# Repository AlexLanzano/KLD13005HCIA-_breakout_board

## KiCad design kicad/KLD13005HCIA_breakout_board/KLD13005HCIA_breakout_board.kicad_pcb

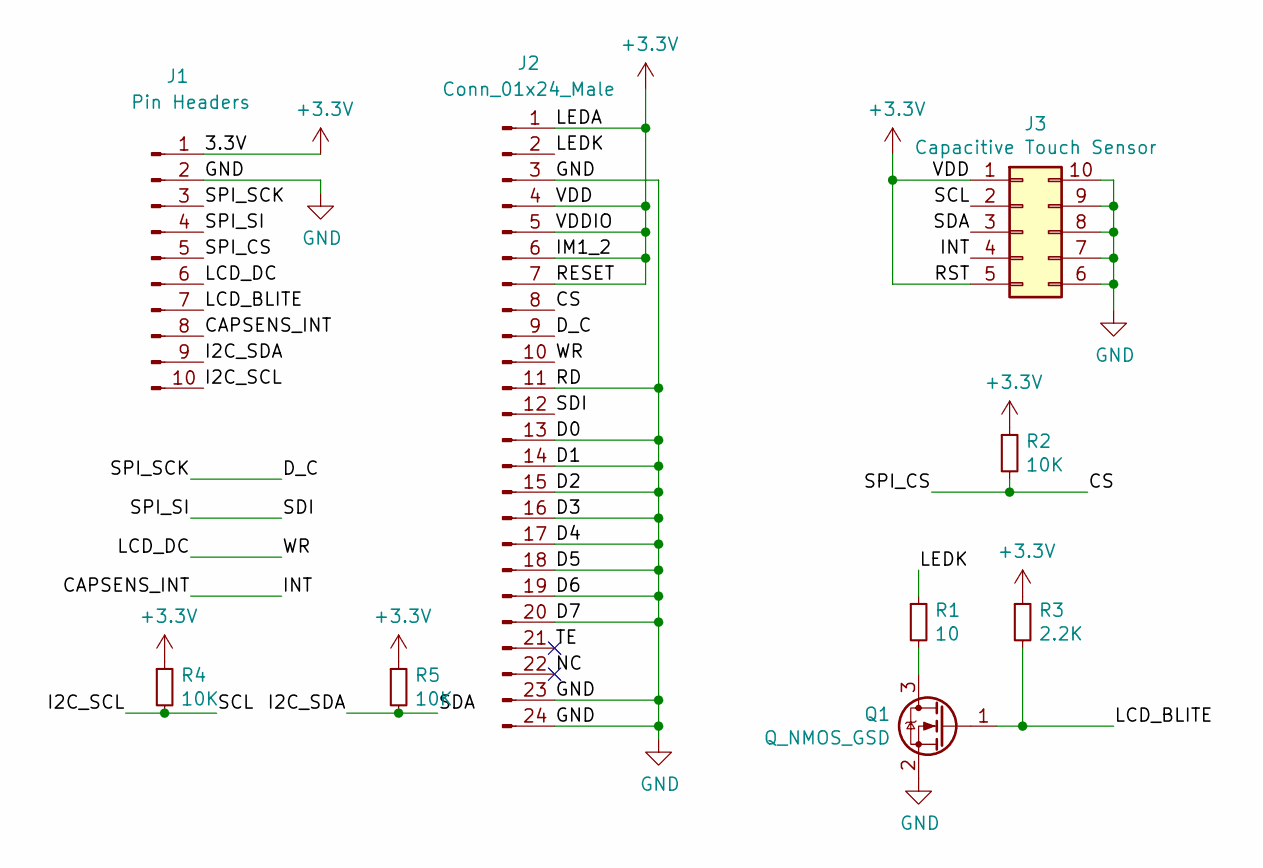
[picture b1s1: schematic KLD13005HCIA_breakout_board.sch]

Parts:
J1: Pin Headers; PinSocket_1x10_P2.54mm_Vertical
J2: Conn_01x24_Male; 687124183622
J3: Capacitive Touch Sensor; BM20B(0.8)-10DS-0.4V(51)
Q1: Q_NMOS_GSD; BSS138
R1: 10; R_0603_1608Metric
R2, R4, R5: 10K; R_0603_1608Metric
R3: 2.2K; R_0603_1608Metric

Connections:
+3V3: J1.1, J2.1, J2.4, J2.5, J2.6, J2.7, J3.1, J3.5, R2.1, R3.1, R4.1, R5.1
/CAPSENS_INT: J1.8, J3.4
/CS: J1.5, J2.8, R2.2
/D_C: J1.3, J2.9
/I2C_SCL: J1.10, J3.2, R4.2
/I2C_SDA: J1.9, J3.3, R5.2
/LCD_BLITE: J1.7, Q1.1 (G), R3.2
/LCD_DC: J1.6, J2.10
/LEDK: J2.2, R1.1
/NC: J2.22
/SDI: J1.4, J2.12
/TE: J2.21
GND: J1.2, J2.3, J2.11, J2.13, J2.14, J2.15, J2.16, J2.17, J2.18, J2.19, J2.20, J2.23, J2.24, J3.6, J3.7, J3.8, J3.9, J3.10, Q1.2 (S)
unnamed: Q1.3 (D), R1.2

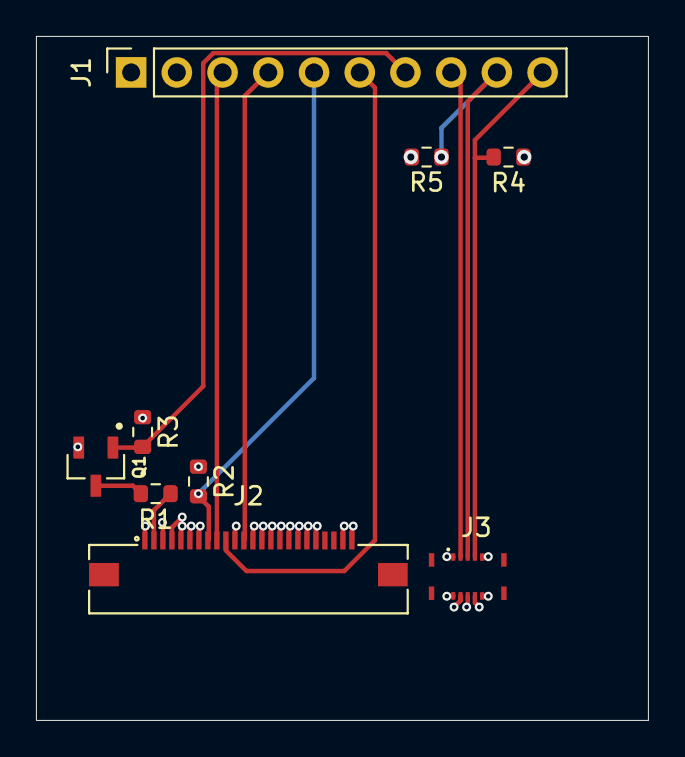
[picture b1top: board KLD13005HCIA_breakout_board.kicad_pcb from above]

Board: 4 copper layers, 34.0 x 38.0 mm, 9 parts (0 on the bottom side), 12 nets.

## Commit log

2021-09-17 Create Makefile for project
2021-09-18 Create schematic
2021-09-20 Create initial PCB design
2021-10-26 Finish initial PCB design
2021-11-10 Update schematic. Move connector position
2021-12-02 Fix pin arrangement for capacitive touch sensor. Rename D/C pin to SCK
2021-12-18 Swap INT and SDC pin labels. Add two 10K pull-up resistors for I2C communication
